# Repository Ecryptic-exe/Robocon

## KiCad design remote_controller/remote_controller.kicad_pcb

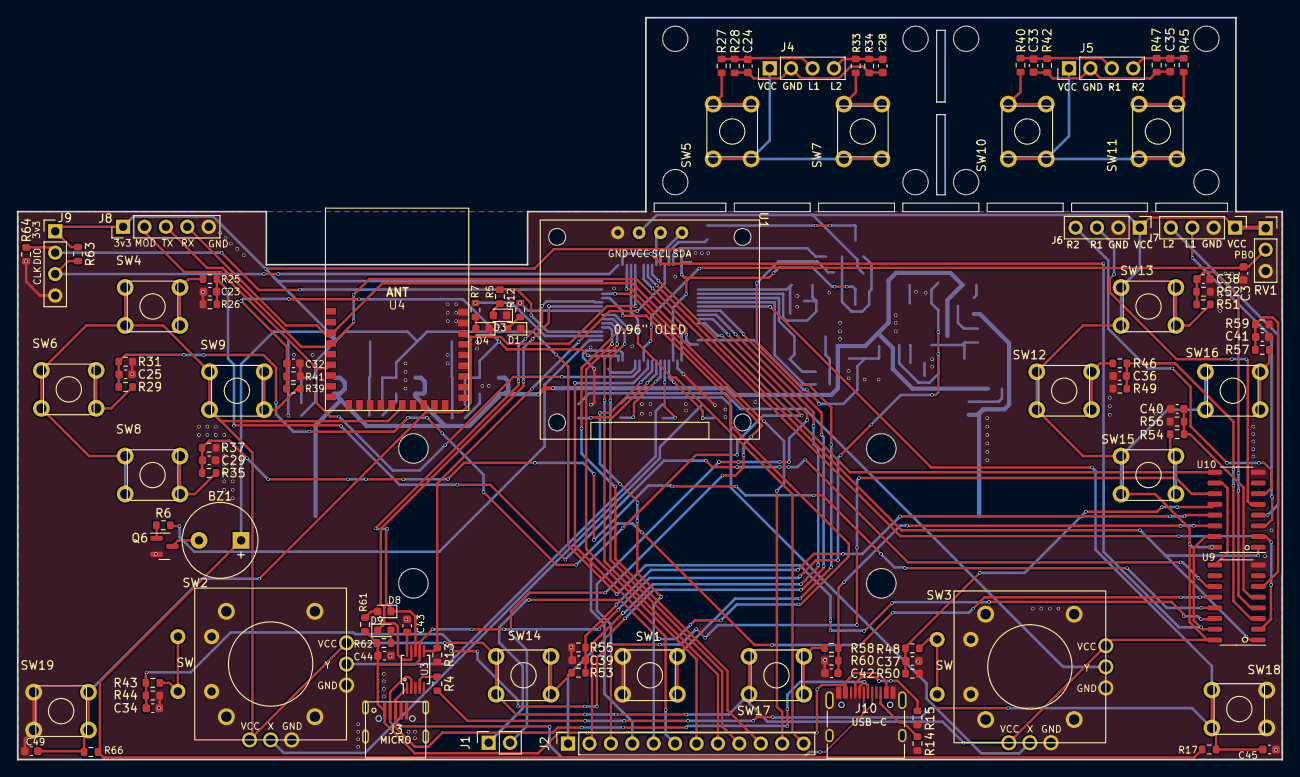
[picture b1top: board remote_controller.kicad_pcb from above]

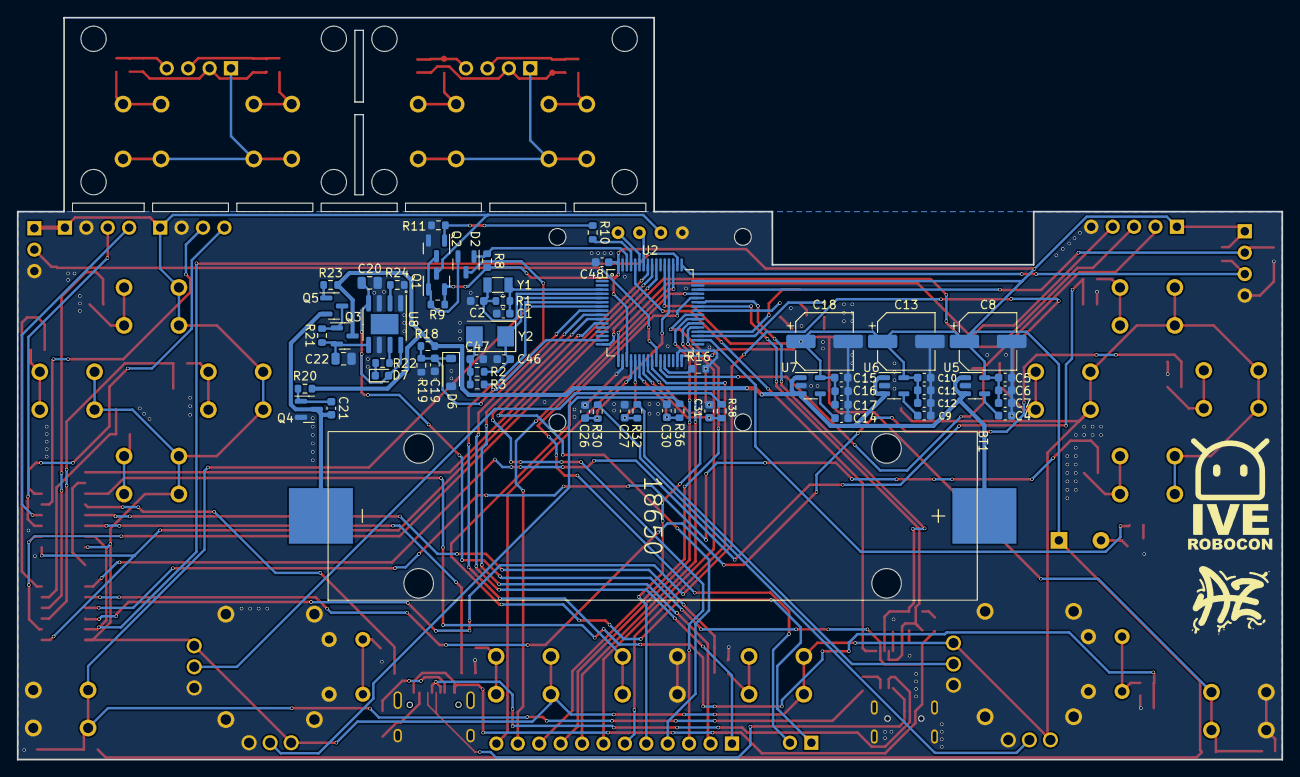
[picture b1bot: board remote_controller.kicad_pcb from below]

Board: 2 copper layers, 150.0 x 88.0 mm, 172 parts (63 on the bottom side), 125 nets.

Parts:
BT1: 18650
BZ1: Buzzer; Buzzer_9x5.5RM5.0
C1, C2: 12.5p; C_0603_1608Metric
C3, C21, C48: 100n; C_0603_1608Metric
C4, C9, C14: 470p; C_0603_1608Metric
C5, C10, C15: 1n; C_0603_1608Metric
C6, C11, C16, C19: 10n; C_0603_1608Metric
C7, C12, C17: 2.2u; C_0603_1608Metric
C8, C13, C18: 220u; CP_Elec_6.3x5.4
C20, C22: 10u; C_0805_2012Metric
C23, C24, C25, C26, C27, C28, C29, C30, C31, C32, C33, C34, C35, C36, C37, C38, C39, C40, C41, C42: C_Small; C_0603_1608Metric
C43, C44: 0.1u; C_0603_1608Metric
C45, C49: 1u; C_0603_1608Metric
C46, C47: 20p; C_0603_1608Metric
D1: Red; LED_0603_1608Metric
D2: BAV70; SOT-23
D3: Yellow; LED_0603_1608Metric
D4: Green; LED_0603_1608Metric
D6: 3v6; D_SOD-123
D7: CHRG; LED_0603_1608Metric
D8: YELLOW; LED_0603_1608Metric
D9: GREEN; LED_0603_1608Metric
J1: Conn_01x02_Socket; PinSocket_1x02_P2.54mm_Vertical
J2: Conn_01x12_Socket; PinSocket_1x12_P2.54mm_Vertical
J3: USB_B_Micro; USB_Micro_5p
J4, J5, J6, J7, J9: Conn_01x04_Pin; PinHeader_1x04_P2.54mm_Vertical
J8: BLE; PinHeader_1x05_P2.54mm_Vertical
J10: USB_C_Receptacle; USB_C_Receptacle_16P_4H
Q1, Q3: AO3401A; SOT-23
Q2, Q4, Q5, Q6: AO3400A; SOT-23
R1, R2: 1M; R_0603_1608Metric
R3: 0; R_0603_1608Metric
R4, R5, R7, R10, R12, R22, R23: 1k; R_0603_1608Metric
R6: 220; R_0603_1608Metric
R8, R9, R11, R17, R19, R21, R63, R64, R66: 10k; R_0603_1608Metric
R13: 4k7; R_0603_1608Metric
R14, R15: 5k1; R_0603_1608Metric
R16, R18: 100k; R_0603_1608Metric
R20: 10; R_0603_1608Metric
R24, R61, R62: 2k; R_0603_1608Metric
R25, R26, R27, R28, R29, R30, R31, R32, R33, R34, R35, R36, R37, R38, R39, R40, R41, R42, R43, R44, R45, R46, R47, R48, R49, R50, R51, R52, R53, R54, R55, R56, R57, R58, R59, R60: R_Small; R_0603_1608Metric
RV1: 10k; PinSocket_1x03_P2.54mm_Vertical
SW1: Home; SW-6-6
SW2, SW3: joystick; joystick2
SW4: Up; SW-6-6
SW5: L1; SW-6-6
SW6: Left; SW-6-6
SW7: L2; SW-6-6
SW8: Down; SW-6-6
SW9: Right; SW-6-6
SW10: R1; SW-6-6
SW11: R2; SW-6-6
SW12: X; SW-6-6
SW13: Y; SW-6-6
SW14: Estop; SW-6-6
SW15: A; SW-6-6
SW16: B; SW-6-6
SW17: Hold; SW-6-6
SW18: Reset; SW-6-6
SW19: BLE_RST; SW-6-6
U1: 0.96"-OLED; 0.96-OLED
U2: STM32F446RCTx; LQFP-64_10x10mm_P0.5mm
U3: CH340X; MSOP-10_3x3mm_P0.5mm
U4: E104-BT53C3
U5, U6, U7: MIC5219-3.3YM5; SOT-23-5
U8: TP4056; SOIC-8-1EP_3.9x4.9mm_P1.27mm_EP2.41x3.3mm
U9, U10: 74HC165; SO-16_3.9x9.9mm_P1.27mm
Y1: 32k768; Crystal_SMD_3215-2Pin_3.2x1.5mm
Y2: 8M; Crystal_SMD_5032-2Pin_5.0x3.2mm

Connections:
+3V3: BZ1.1 (-), C5.1, C6.1, C7.1, C8.1, C10.1, C11.1, C12.1, C13.1, C15.1, C16.1, C17.1, C18.1, C48.1, J8.1, J9.1, Q1.2 (S), R8.2, R9.2, R17.1, R63.1, R66.1, U2.19 (VDD), U2.32 (VDD), U2.48 (VDD), U2.64 (VDD), U5.5 (OUT), U6.5 (OUT), U7.5 (OUT)
+5V: C20.1, C44.2, D7.2 (A), J3.1 (VBUS), J10.A4 (VBUS), J10.A9 (VBUS), J10.B4 (VBUS), J10.B9 (VBUS), R61.1, R62.1, U3.7 (VCC), U8.4 (VCC), U8.8 (CE)
+BATT: BT1.1 (+), Q3.3 (D), R18.1, R20.1, R23.2, U5.1 (IN), U5.3 (EN), U6.1 (IN), U6.3 (EN), U7.1 (IN), U7.3 (EN)
-BATT: BT1.2 (-), C21.2, Q4.3 (D), Q5.2 (S)
/BLE_RESET: C49.1, R66.2, SW19.2, SW19.4, U2.53 (PC12), U4.26 (RESET)
/BOOT0: R13.1, U2.60 (BOOT0), U3.6 (TNOW/~DTR)
/BOOT1: R16.1, U2.28 (PB2)
/CP: U2.55 (PB3), U9.2 (CP), U10.2 (CP)
/I2C1_SCL: U1.3 (SCL), U2.58 (PB6)
/I2C1_SDA: U1.4 (SDA), U2.59 (PB7)
/MOD: J8.2, U2.27 (PB1), U4.6 (MOD)
/OSC32_IN: C1.1, R1.1, U2.3 (PC14), Y1.2
/OSC32_OUT: C2.1, R1.2, U2.4 (PC15), Y1.1
/OSC_IN: C46.1, R2.1, U2.5 (PH0), Y2.1
/OSC_OUT: R3.2, U2.6 (PH1)
/PA8: R12.2, U2.41 (PA8)
/PA11: J1.1, U2.44 (PA11)
/PA12: J1.2, U2.45 (PA12)
/PB0: C3.1, RV1.2, U2.26 (PB0)
/PB13: R6.2, U2.34 (PB13)
/PB14: R7.2, U2.35 (PB14)
/PB15: R5.2, U2.36 (PB15)
/PC0: J2.1, U2.8 (PC0)
/PC1: J2.2, U2.9 (PC1)
/PC2: J2.3, U2.10 (PC2)
/PC3: J2.4, U2.11 (PC3)
/PC4: J2.5, U2.24 (PC4)
/PC5: J2.6, U2.25 (PC5)
/PC6: J2.7, U2.37 (PC6)
/PC7: J2.8, U2.38 (PC7)
/PC8: J2.9, U2.39 (PC8)
/PC9: J2.10, U2.40 (PC9)
/PC10: J2.11, U2.51 (PC10)
/PC11: J2.12, U2.52 (PC11)
/PG1: D2.1 (A), R8.1, U2.62 (PB9)
/PG2: R10.2, U2.61 (PB8)
/Q7_1: U2.57 (PB5), U10.9 (Q7)
/RST: C45.1, R4.2, R17.2, SW18.2, SW18.4, U2.7 (NRST)
/SWCLK: J9.3, R63.2, U2.49 (PA14)
/SWDIO: J9.2, R64.1, U2.46 (PA13)
/UART1_RX: D8.1 (K), U2.43 (PA10), U3.8 (TXD)
/UART1_TX: D9.1 (K), U2.42 (PA9), U3.9 (RXD)
/UART2_RX: J8.4, U2.17 (PA3), U4.3 (TXD)
/UART2_TX: J8.3, U2.16 (PA2), U4.4 (RXD)
/buttons/D0_0: C23.1, R25.2, R26.2, U9.11 (D0)
/buttons/D0_1: C34.1, R43.2, R44.2, U10.11 (D0)
/buttons/D1_0: C25.1, R29.2, R31.2, U9.12 (D1)
/buttons/D1_1: C37.1, R48.2, R50.2, U10.12 (D1)
/buttons/D2_0: C29.1, R35.2, R37.2, U9.13 (D2)
/buttons/D2_1: C39.1, R53.2, R55.2, U10.13 (D2)
/buttons/D3_0: C32.1, R39.2, R41.2, U9.14 (D3)
/buttons/D3_1: C42.1, R58.2, R60.2, U10.14 (D3)
/buttons/D4_0: C36.1, R46.2, R49.2, U9.3 (D4)
/buttons/D4_1: J7.3, U10.3 (D4)
/buttons/D5_0: C38.1, R51.2, R52.2, U9.4 (D5)
/buttons/D5_1: J7.4, U10.4 (D5)
/buttons/D6_0: C40.1, R54.2, R56.2, U9.5 (D6)
/buttons/D6_1: J6.3, U10.5 (D6)
/buttons/D7_0: C41.1, R57.2, R59.2, U9.6 (D7)
/buttons/D7_1: J6.4, U10.6 (D7)
/buttons/Q7_0: U9.9 (Q7), U10.10 (DS)
/buttons/SW1: R43.1, SW2.5 (SW)
/buttons/SW2: R48.1, SW3.5 (SW)
/buttons/X1: R30.1, SW2.3 (VRx)
/buttons/X1_filtered: C26.1, R30.2, U2.20 (PA4)
/buttons/X2: R36.1, SW3.3 (VRx)
/buttons/X2_filtered: C30.1, R36.2, U2.22 (PA6)
/buttons/Y1: R32.1, SW2.4 (VRy)
/buttons/Y1_filtered: C27.1, R32.2, U2.21 (PA5)
/buttons/Y2: R38.1, SW3.4 (VRy)
/buttons/Y2_filtered: C31.1, R38.2, U2.23 (PA7)
/buttons/conn_gnd_L: C24.2, C28.2, J4.2, R28.1, R34.1
/buttons/conn_gnd_R: C33.2, C35.2, J5.2, R42.1, R47.1
/buttons/conn_vcc_L: J4.1, SW5.1, SW5.3, SW7.1, SW7.3
/buttons/conn_vcc_R: J5.1, SW10.1, SW10.3, SW11.1, SW11.3
/power_part/BAT_VOLT: C19.1, D6.1 (K), R18.2, R19.1, U2.15 (PA1)
/power_part/D+: J3.3 (D+), J10.A6 (D+), J10.B6 (D+), U3.1 (UD+)
/power_part/D-: J3.2 (D-), J10.A7 (D-), J10.B7 (D-), U3.2 (UD-)
/usb2ttl/~RTS: R4.1, U3.4 (~RTS)
/~CE: U2.50 (PA15), U9.15 (~CE), U10.15 (~CE)
/~PL: U2.56 (PB4), U9.1 (~PL), U10.1 (~PL)
GND: C1.2, C2.2, C3.2, C4.2, C5.2, C6.2, C7.2, C8.2, C9.2, C10.2, C11.2, C12.2, C13.2, C14.2, C15.2, C16.2, C17.2, C18.2, C19.2, C20.2, C22.2, C23.2, C25.2, C26.2, C27.2, C29.2, C30.2, C31.2, C32.2, C34.2, C36.2, C37.2, C38.2, C39.2, C40.2, C41.2, C42.2, C43.2, C44.1, C45.2, C46.2, C47.2, C48.2, C49.2, D1.1 (K), D3.1 (K), D4.1 (K), D6.2 (A), J3.5 (GND), J3.6 (Shield), J6.2, J7.2, J8.5, J9.4, J10.A1 (GND), J10.A12 (GND), J10.B1 (GND), J10.B12 (GND), J10.S1 (SHIELD), Q2.2 (S), Q4.2 (S), Q6.2 (S), R11.1, R13.2, R14.1, R15.1, R16.2, R19.2, R24.1, R26.1, R31.1, R37.1, R41.1, R44.1, R49.1, R50.1, R52.1, R55.1, R56.1, R59.1, R60.1, R64.2, RV1.3, SW1.1, SW1.3, SW2.1 (GND), SW2.6 (Shield), SW3.1 (GND), SW3.6 (Shield), SW18.1, SW18.3, SW19.1, SW19.3, U1.1 (GND), U2.12 (VSSA), U2.18 (VSS), U2.31 (VSS), U2.47 (VSS), U2.63 (VSS), U3.3 (GND), U4.27 (GND), U4.28 (GND), U5.2 (GND), U6.2 (GND), U7.2 (GND), U8.1 (Temp), U8.3 (GND), U8.6 (STDBY), U9.8 (GND), U10.8 (GND)
unnamed: BZ1.2 (+), Q6.3 (D)
unnamed: C47.1, R2.2, R3.1, Y2.2
unnamed: D1.2 (A), R12.1
unnamed: D2.3 (K), SW1.2, SW1.4
unnamed: D3.2 (A), R5.1
unnamed: D4.2 (A), R7.1
unnamed: D7.1 (K), R22.1
unnamed: D8.2 (A), R61.2
unnamed: D9.2 (A), R62.2
unnamed: C24.1, J4.3, R27.2, R28.2
unnamed: C28.1, J4.4, R33.2, R34.2
unnamed: C33.1, J5.3, R40.2, R42.2
unnamed: C35.1, J5.4, R45.2, R47.2
unnamed: J10.A5 (CC1), R15.2
unnamed: J10.B5 (CC2), R14.2
unnamed: D2.2 (A), Q1.1 (G), Q2.3 (D), R9.1
unnamed: Q2.1 (G), R10.1, R11.2
unnamed: Q3.1 (G), Q5.3 (D), R21.2
unnamed: C22.1, Q3.2 (S), R21.1, U8.5 (BAT)
unnamed: C21.1, Q4.1 (G), R20.2
unnamed: Q5.1 (G), R23.1
unnamed: Q6.1 (G), R6.1
unnamed: R25.1, SW4.2, SW4.4
unnamed: R27.1, SW5.2, SW5.4
unnamed: R29.1, SW6.2, SW6.4
unnamed: R33.1, SW7.2, SW7.4
unnamed: R35.1, SW8.2, SW8.4
unnamed: R39.1, SW9.2, SW9.4
unnamed: R40.1, SW10.2, SW10.4
unnamed: R45.1, SW11.2, SW11.4
unnamed: R46.1, SW12.2, SW12.4
unnamed: R51.1, SW13.2, SW13.4
unnamed: R53.1, SW14.2, SW14.4
unnamed: R54.1, SW15.2, SW15.4
unnamed: R57.1, SW16.2, SW16.4
unnamed: R58.1, SW17.2, SW17.4
unnamed: C43.1, U3.10 (V3)
unnamed: C4.1, U5.4 (BP)
unnamed: C9.1, U6.4 (BP)
unnamed: C14.1, U7.4 (BP)
unnamed: R22.2, U8.7 (CHRG)
unnamed: R24.2, U8.2 (PROG)
VCC: J6.1, J7.1, Q1.3 (D), RV1.1, SW2.2 (Vcc), SW3.2 (Vcc), SW4.1, SW4.3, SW6.1, SW6.3, SW8.1, SW8.3, SW9.1, SW9.3, SW12.1, SW12.3, SW13.1, SW13.3, SW14.1, SW14.3, SW15.1, SW15.3, SW16.1, SW16.3, SW17.1, SW17.3, U1.2 (Vcc), U4.15 (VCC), U9.16 (VCC), U10.16 (VCC)

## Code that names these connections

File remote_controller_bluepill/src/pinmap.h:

#ifndef PINMAP_H
#define PINMAP_H

#define PG1 PB9
#define PG2 PB8

#define I2C1_SDA PB7
#define I2C1_SCL PB6

#define butts_data_pin PB5
#define nPL PB4
#define CP PB3
#define nCE PA15

#define variable_r PB0

#define uart1_tx PA9
#define uart1_rx PA10

#define uart2_tx PA2
#define uart2_rx PA3

#define battery_level PA1 

#define led1 PA8
#define led2 PB15
#define led3 PB14
#define buzzer PB13

#define BLE_reset PA11
#define BLE_Mod PB12

#define X1_pin PA4
#define Y1_pin PA5
#define X2_pin PA6
#define Y2_pin PA7

#endif

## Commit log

2024-04-11 mbed code wip
2024-04-11 pcb
    refer to remote controller
2024-04-11 mbed code wip ver2
2024-04-16 mbed debug
2024-04-16 mbed
2024-04-24 mbed stm32f446
2024-04-30 Solidworks Remote Case V1
2024-05-23 Arduino Code Bluepill
2024-05-23 Controller V2, f446 not working
2024-05-31 Arduino Bluepill
    Send through BLE tested, kinda works, can't view received data from bot
    Added hold home to view robot details (just have to remind that don't hold so long since the remote will turn off)
2024-06-04 test ble bluepill arduino
